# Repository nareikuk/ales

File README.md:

# ales
Altitude Limiting Electronic Switch for model electric glider competitions

This is still under early development even though it has been under construction since 2016. The aim is to produce a cheap,
easy to construct and simple to use altitude limiting switch for electric motor launched model gliders for competition use.
The schematics, PCB and firmware are all provided. I may be able to supply blank PCBs or even fully populated PCBs in the future,
once the bugs have been ironed out and I'm happy that the project has reached a production quality level.

Note that currently the firmware is working but some improvements required around startup reliability.

The current features of the ALES v2 include:
1) Pre-set altitude cut-off of 100m, 150m or 200m which are the three standards used in competition.
2) Motor run time limited to 30 seconds if pre-set altitude has not been reached before then
3) Auto-calibrates to receiver pulse timing at start up
4) Auto-calibrates altitude of launch field
5) After cut-off, if throttle stick is retuned to idle, the ALES will re-enable motor power after three seconds for those landing emergencies
6) Altitude sampling at 1kHz with better than 0.2m resolution
7) Very small and light hardware profile
8) Works with HV or standard servos and is powered from the receiver, drawing around 2mA
9) 32-bit STM32F0 microcontroller and BMP280 pressure sensor provide the core functionality
10) Single-sided load for all surface mount components

Future features once v2 has reached production quality will include anti-zoom control and field based configuration.

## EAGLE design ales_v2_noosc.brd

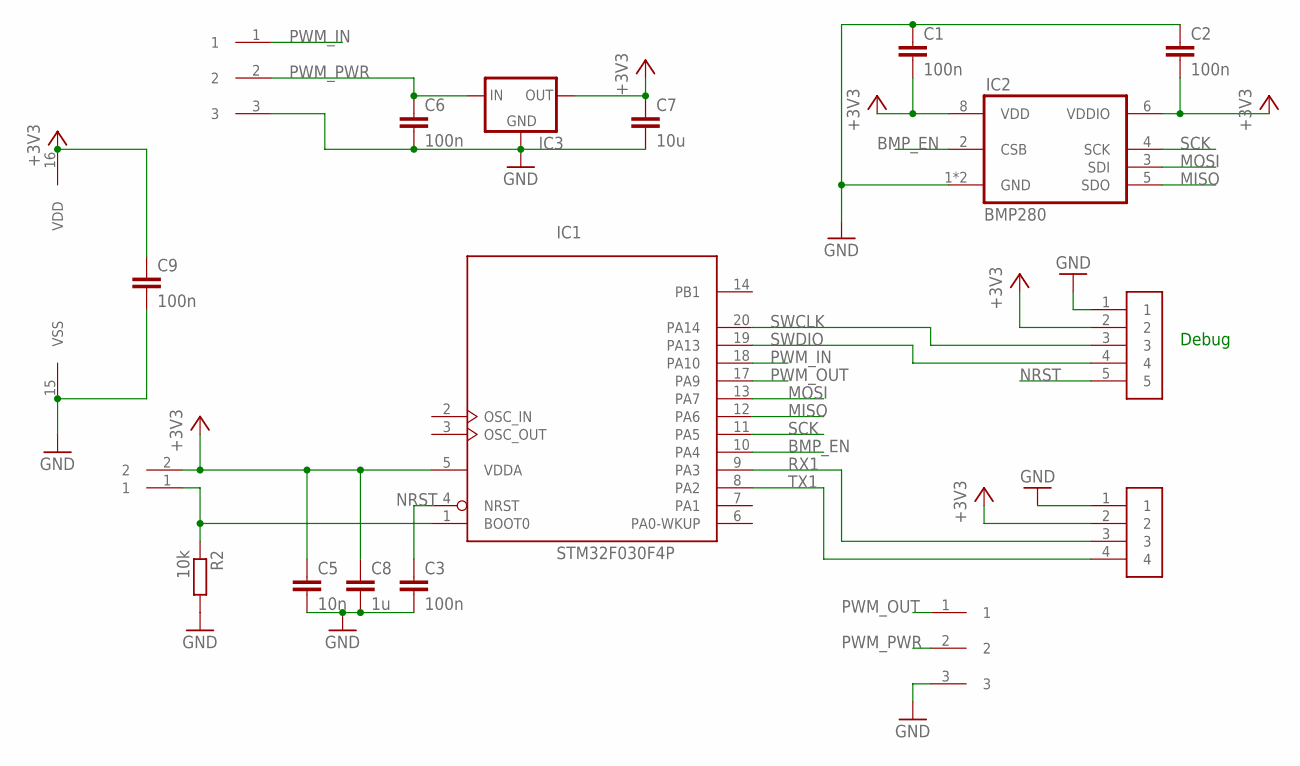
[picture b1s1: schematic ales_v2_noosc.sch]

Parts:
BOOT: SMD_CONN1X2; CONN_SMD1X2
C1, C2, C3, C6, C9: 100n; C0603K
C5: 10n; C0603K
C7: 10u; C0603K
C8: 1u; C0603K
IC1: STM32F030F4P; TSSOP20-I
IC2: BMP280
IC3: XC63FPM; SOT23
R2: 10k; R0603
U$2, U$3: CONN1X3
U$4: CONN1X4
U$6: CONN1X5

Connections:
+3V3: BOOT.2, C1.2, C2.2, C5.1, C7.1, C8.1, C9.1, IC1.5 (VDDA), IC1.16 (VDD), IC2.6 (VDDIO), IC2.8 (VDD), IC3.1 (OUT), U$4.2, U$6.2
BMP_EN: IC1.10 (PA4), IC2.2 (CSB)
BOOT0: BOOT.1, IC1.1 (BOOT0), R2.1
GND: C1.1, C2.1, C3.2, C5.2, C6.2, C7.2, C8.2, C9.2, IC1.15 (VSS), IC2.1 (GND), IC2.7 (GND), IC3.3 (GND), R2.2, U$2.3, U$3.3, U$4.1, U$6.1
MISO: IC1.12 (PA6), IC2.5 (SDO)
MOSI: IC1.13 (PA7), IC2.3 (SDI)
NRST: C3.1, IC1.4 (NRST), U$6.5
PWM_IN: IC1.18 (PA10), U$3.1
PWM_OUT: IC1.17 (PA9), U$2.1
PWM_PWR: C6.1, IC3.2 (IN), U$2.2, U$3.2
RX1: IC1.9 (PA3), U$4.3
SCK: IC1.11 (PA5), IC2.4 (SCK)
SWCLK: IC1.20 (PA14), U$6.3
SWDIO: IC1.19 (PA13), U$6.4
TX1: IC1.8 (PA2), U$4.4

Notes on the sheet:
Debug

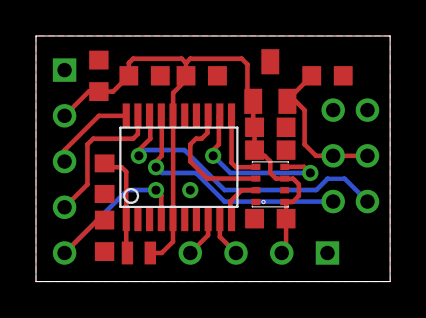
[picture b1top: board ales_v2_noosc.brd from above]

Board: 2 copper layers, 19.7 x 13.6 mm, 17 parts (0 on the bottom side), 15 nets.

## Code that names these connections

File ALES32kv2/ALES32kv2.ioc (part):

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Mcu.Name=STM32F031F(4-6)Px
Mcu.Package=TSSOP20
Mcu.UserName=STM32F031F6Px
PA10.GPIOParameters=GPIO_Label
PA10.GPIO_Label=PWM_IN
PA10.Signal=S_TIM1_CH3
PA13.Mode=Serial_Wire
PA13.Signal=SYS_SWDIO
PA14.Mode=Serial_Wire
PA14.Signal=SYS_SWCLK
PA2.Mode=Asynchronous
PA2.Signal=USART1_TX
PA3.Mode=Asynchronous
PA3.Signal=USART1_RX
PA4.GPIOParameters=GPIO_Label,GPIO_Speed
PA4.GPIO_Label=SPI_EN
PA4.GPIO_Speed=GPIO_SPEED_FREQ_HIGH
PA4.Signal=GPIO_Output
PA5.Mode=Full_Duplex_Master
PA5.Signal=SPI1_SCK
PA6.Mode=Full_Duplex_Master
PA6.Signal=SPI1_MISO
PA7.Mode=Full_Duplex_Master
PA7.Signal=SPI1_MOSI
PA9.GPIOParameters=GPIO_Label,GPIO_Speed
PA9.GPIO_Label=PWM_OUT
PA9.GPIO_Speed=GPIO_SPEED_FREQ_HIGH
PA9.Signal=S_TIM1_CH2
PB1.GPIOParameters=GPIO_Label
PB1.GPIO_Label=LOOP_TICK
PB1.Signal=GPIO_Output
RCC.SYSCLKFreq_VALUE=48000000
RCC.SYSCLKSource=RCC_SYSCLKSOURCE_PLLCLK
board=ALES32kv2

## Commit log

2017-09-08 Initial upload of ALES firmware
2020-07-04 Code updates, now working and formatting
2020-07-04 More tidy-ups, remove logging for perf tests
2020-07-04 test
2020-07-04 Clean up test
